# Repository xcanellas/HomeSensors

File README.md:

## Descripción

Desarrollo de tarjeta electrónica para medir distintos sensores y enviar los datos a traves de WIFI a una base de datos para su posterior tratamiento y visualizacion via WEB.

## Autor
**Xavier Cañellas**

* [Linkedin] (https://www.linkedin.com/in/xcanellas/)
* [Proyectos personales] (http://xnmundo.com/)

## Contacto
Si quieres contactarme puedes escribirme a xcanellas@xnmundo.com para consultas.

## Lincencia
MIT Public License v3.0
No puede usarse comercialmente.

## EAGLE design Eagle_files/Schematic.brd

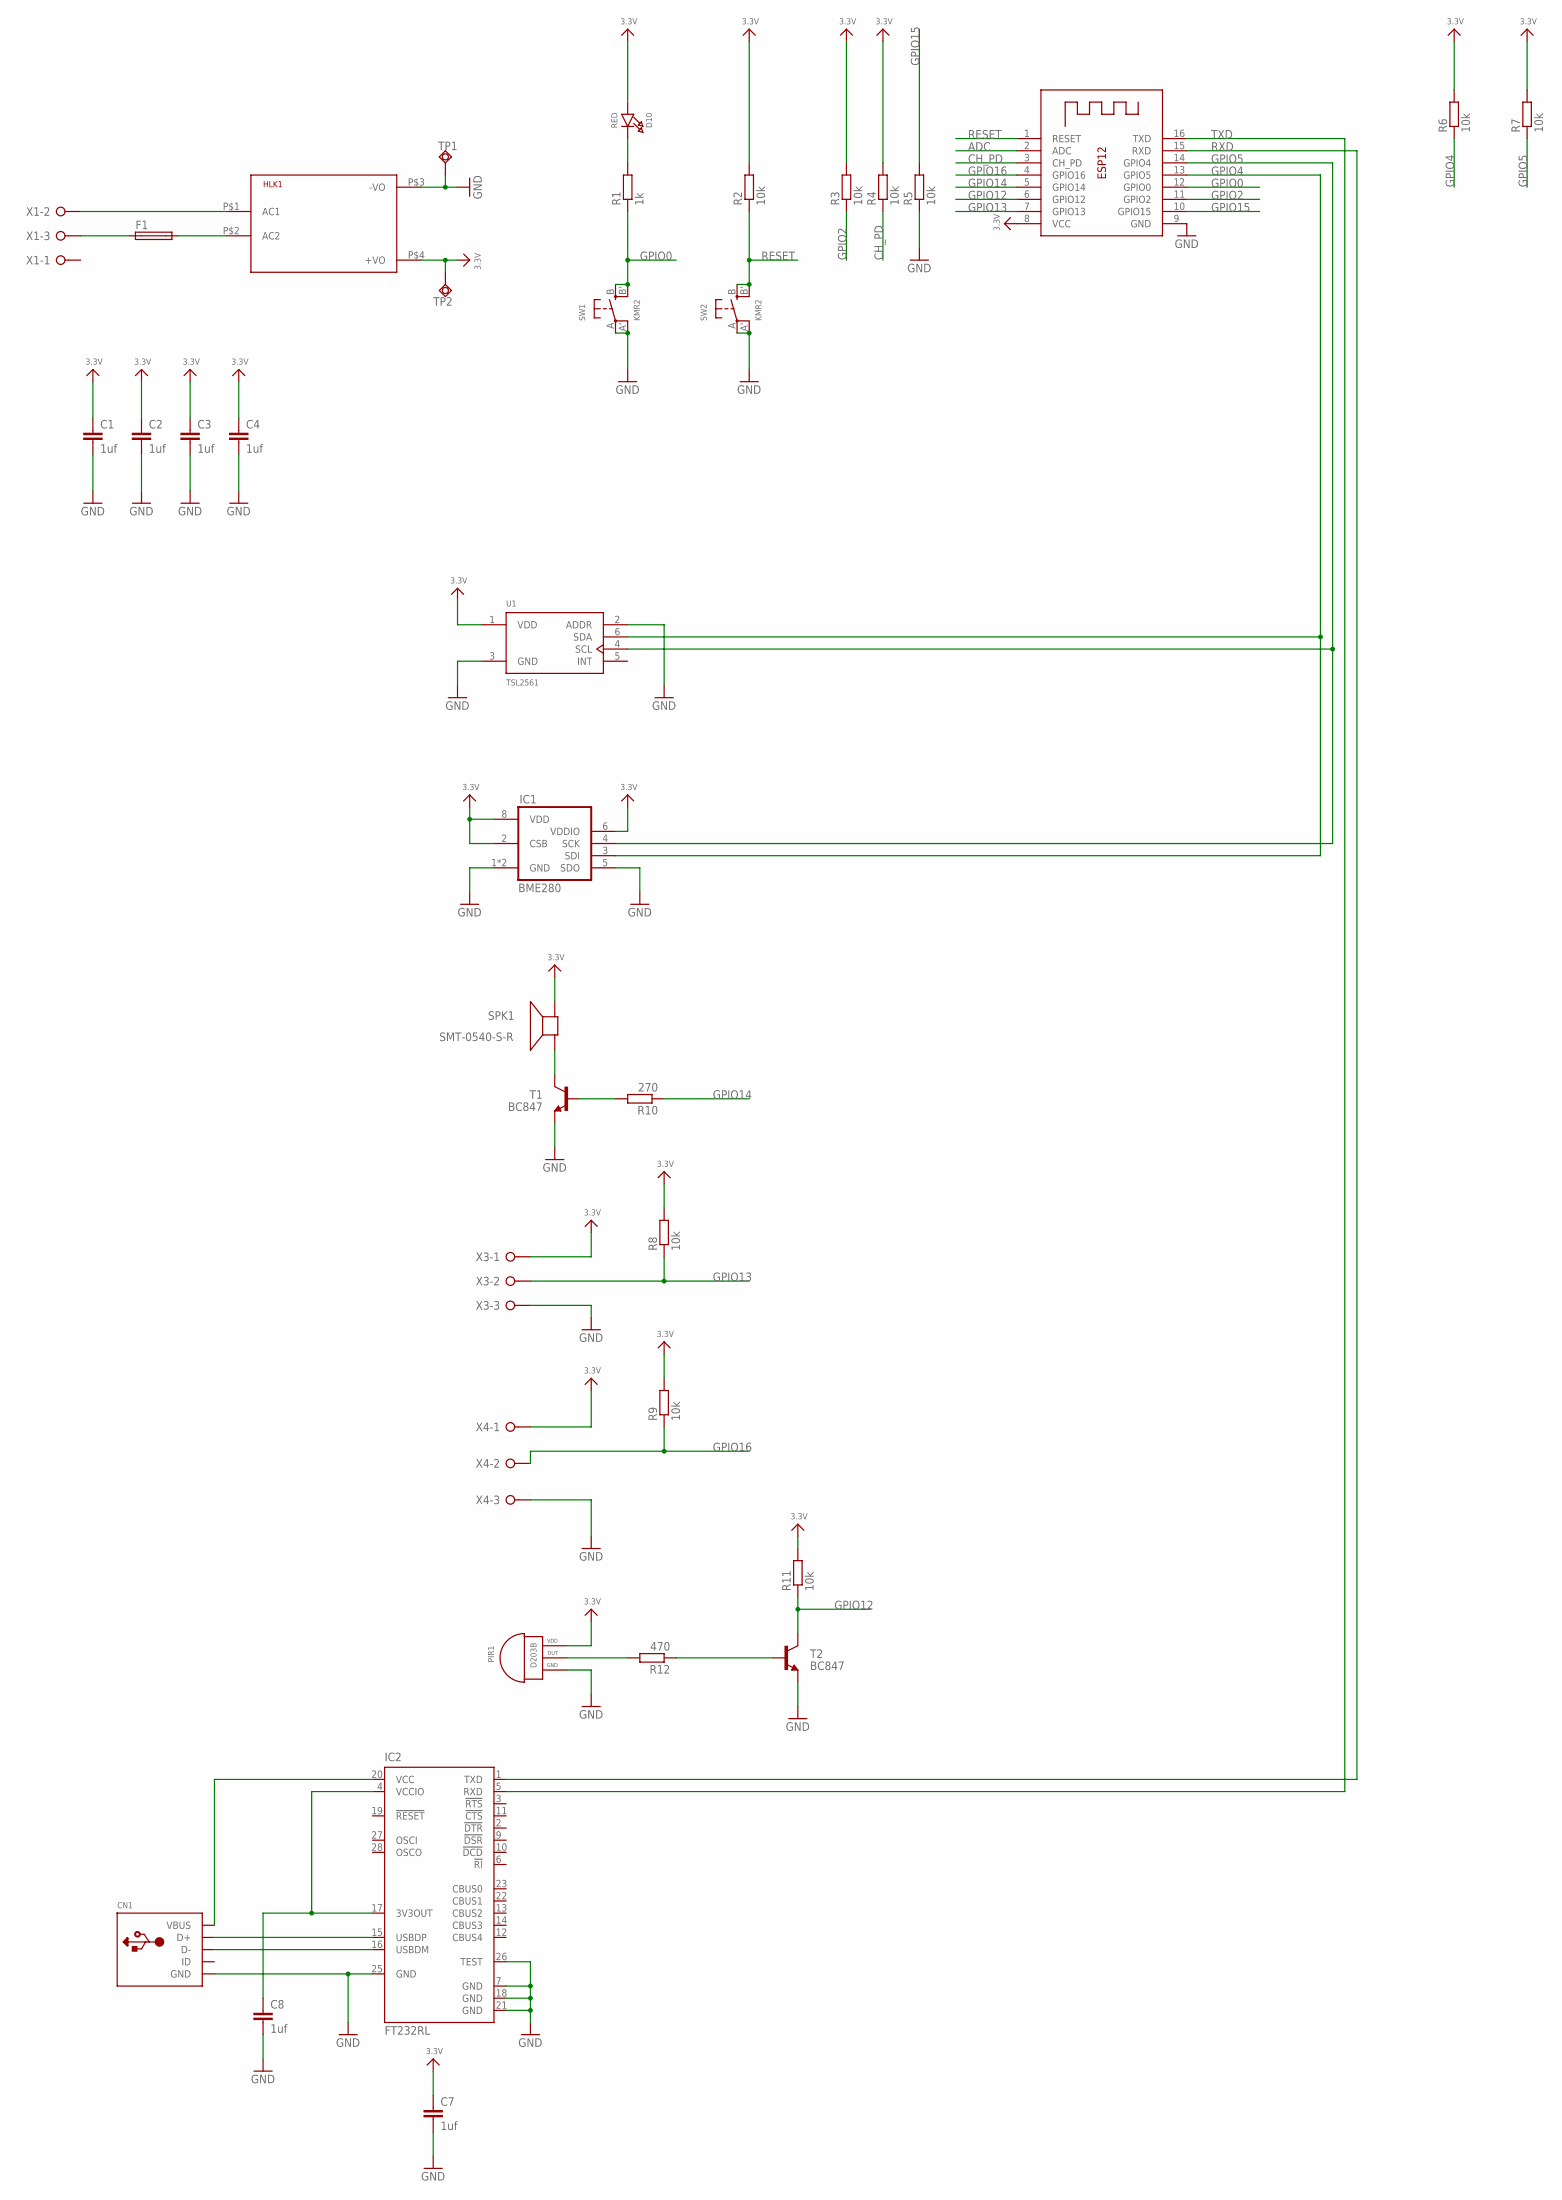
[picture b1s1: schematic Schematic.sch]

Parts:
C1, C2, C3, C4, C7, C8: 1uf; C0805
CN1: USBMINIB; USB-MINIB
D10: RED; CHIPLED_0805_NOOUTLINE
F1: SH22
HLK1: HLK-PM013W; HLK-PM01
IC1: BME280
IC2: FT232RL; SSOP28
PIR1: D203B; 3PIN
R1: 1k; M0805
R2, R3, R4, R5, R6, R7, R8, R9, R11: 10k; M0805
R10: 270; M0805
R12: 470; M0805
SPK1: SMT-0540-S-R
SW1, SW2: KMR2; BTN_KMR2_4.6X2.8
T1, T2: BC847; SOT23
TP1, TP2: TPSQPAD1-13Y; P1-13Y
U1: TSL2561; TMB-6
X1, X3, X4: W237-03P; W237-133
X2: ESP-12

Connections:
3.3V: C1.1, C2.1, C3.1, C4.1, C7.1, D10.A, HLK1.P$4 (+VO), IC1.2 (CSB), IC1.6 (VDDIO), IC1.8 (VDD), PIR1.1 (VDD), R2.2, R3.2, R4.2, R6.2, R7.2, R8.2, R9.2, R11.2, SPK1.+ (-), TP2.TP, U1.1 (VDD), X2.8 (VCC), X3.1, X4.1
ADC: X2.2 (ADC)
CH_PD: R4.1, X2.3 (CH_PD)
GND: C1.2, C2.2, C3.2, C4.2, C7.2, C8.2, CN1.GND, HLK1.P$3 (-VO), IC1.1 (GND), IC1.5 (SDO), IC1.7 (GND), IC2.7 (GND), IC2.18 (GND), IC2.21 (GND), IC2.25 (GND), IC2.26 (TEST), PIR1.3 (GND), R5.1, SW1.A, SW1.A' (P1), SW2.A, SW2.A' (P1), T1.2 (E), T2.2 (E), TP1.TP, U1.2 (ADDR), U1.3 (GND), X2.9 (GND), X3.3, X4.3
GPIO0: R1.1, SW1.B (S), SW1.B' (S1), X2.12 (GPIO0)
GPIO2: R3.1, X2.11 (GPIO2)
GPIO4: IC1.3 (SDI), R6.1, U1.6 (SDA), X2.13 (GPIO5)
GPIO5: IC1.4 (SCK), R7.1, U1.4 (SCL), X2.14 (GPIO4)
GPIO12: R11.1, T2.3 (C), X2.6 (GPIO12)
GPIO13: R8.1, X2.7 (GPIO13), X3.2
GPIO14: R10.1, X2.5 (GPIO14)
GPIO15: R5.2, X2.10 (GPIO15)
GPIO16: R9.1, X2.4 (GPIO16), X4.2
unnamed: F1.1, X1.3
unnamed: F1.2, HLK1.P$2 (AC2)
unnamed: HLK1.P$1 (AC1), X1.2
unnamed: D10.C, R1.2
unnamed: SPK1.- (+), T1.3 (C)
unnamed: R10.2, T1.1 (B)
unnamed: PIR1.2 (OUT), R12.2
unnamed: R12.1, T2.1 (B)
unnamed: CN1.D+, IC2.15 (USBDP)
unnamed: CN1.D-, IC2.16 (USBDM)
unnamed: C8.1, IC2.4 (VCCIO), IC2.17 (3V3OUT)
unnamed: CN1.VBUS, IC2.20 (VCC)
RESET: R2.1, SW2.B (S), SW2.B' (S1), X2.1 (RESET)
RXD: IC2.1 (TXD), X2.15 (RXD)
TXD: IC2.5 (RXD), X2.16 (TXD)

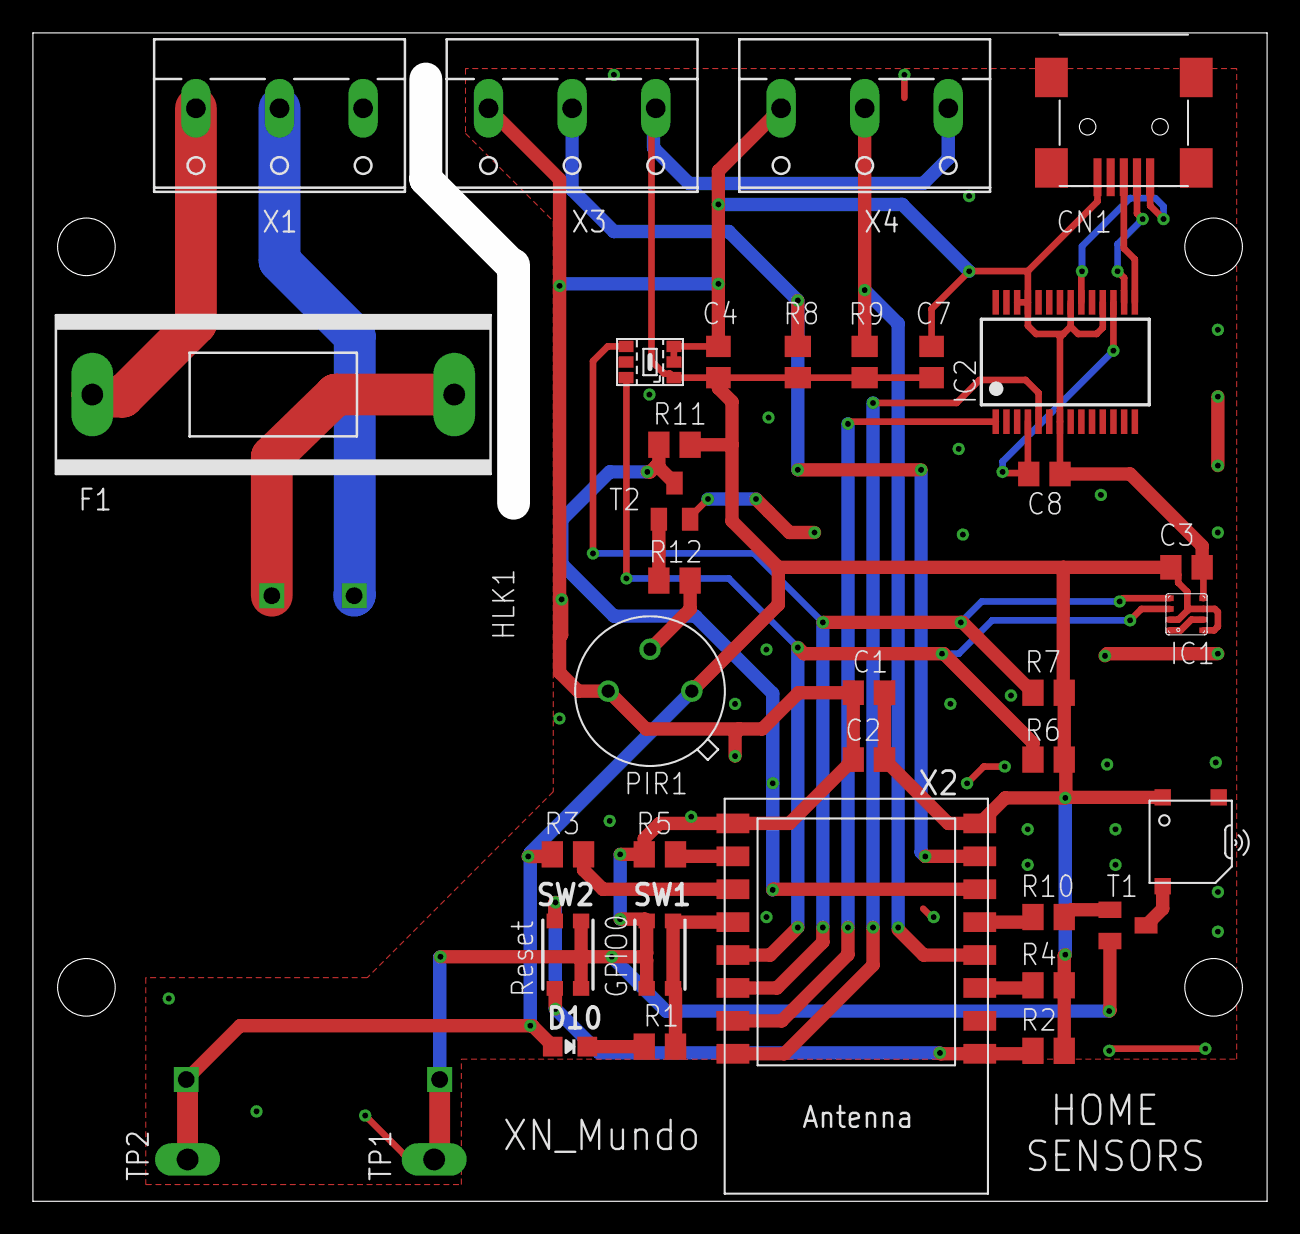
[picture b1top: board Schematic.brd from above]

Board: 2 copper layers, 73.0 x 69.0 mm, 37 parts (0 on the bottom side), 27 nets.

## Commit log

2020-07-24 Added ESP8266 program

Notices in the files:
parts and their libraries:
microbuilder: This work is placed in the public domain, and may be freely used for commercial and non-commercial work with the following conditions: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
eagle-library-edeca.net-v5: This is v1 and is licensed under the Creative Commons (Attribution-Non-Commercial-Share Alike 2.0 UK)
